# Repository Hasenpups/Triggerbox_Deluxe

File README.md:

Shield: [![CC BY-NC-SA 4.0][cc-by-nc-sa-shield]][cc-by-nc-sa]

This work is licensed under a
[Creative Commons Attribution-NonCommercial-ShareAlike 4.0 International License][cc-by-nc-sa].

[![CC BY-NC-SA 4.0][cc-by-nc-sa-image]][cc-by-nc-sa]

[cc-by-nc-sa]: http://creativecommons.org/licenses/by-nc-sa/4.0/
[cc-by-nc-sa-image]: https://licensebuttons.net/l/by-nc-sa/4.0/88x31.png
[cc-by-nc-sa-shield]: https://img.shields.io/badge/License-CC%20BY--NC--SA%204.0-lightgrey.svg

## Donations / Spenden
If somebody wants to support me for upcoming projects :)  
- PayPal:  
- Amazon Giftcard: https://www.amazon.de/Amazon-Gutschein-per-E-Mail-Amazon/dp/B0054PDOV8 - stefan.riese@me.com

# Triggerbox Deluxe

It's a trigger device for multiple devices and input counter.
- Raspberry Pi Pico
- 24V power input
- 8 x optocoupler input
- 8 x high side switch 24V 500mA output
- optional Wifi interface instead of USB connection (ESP32C3)

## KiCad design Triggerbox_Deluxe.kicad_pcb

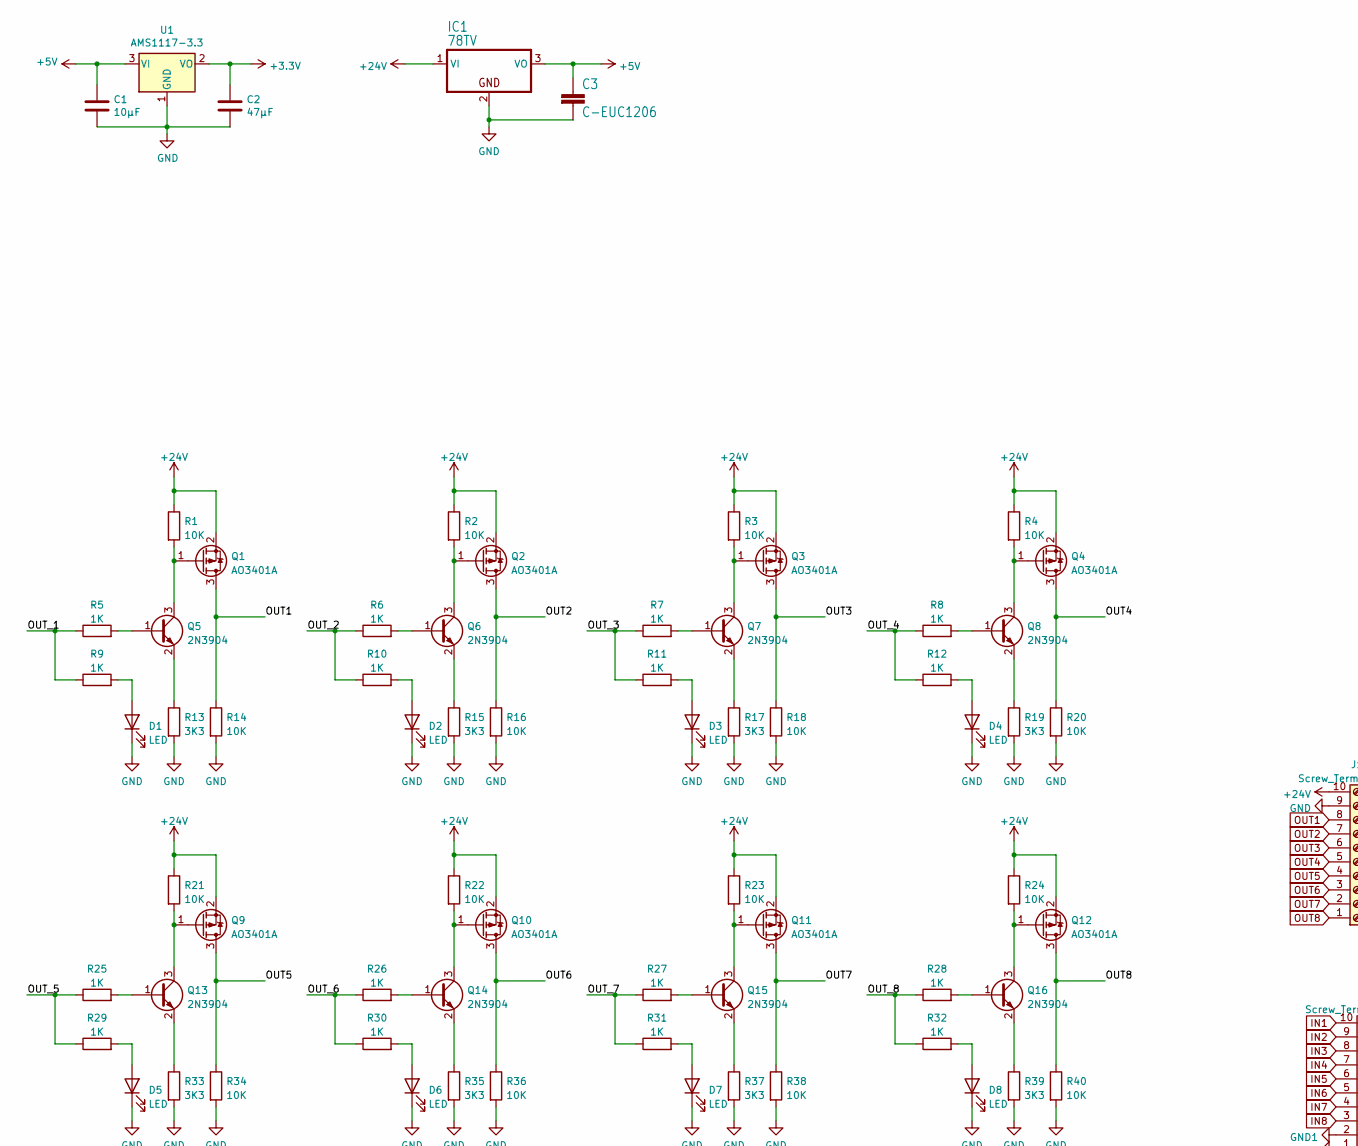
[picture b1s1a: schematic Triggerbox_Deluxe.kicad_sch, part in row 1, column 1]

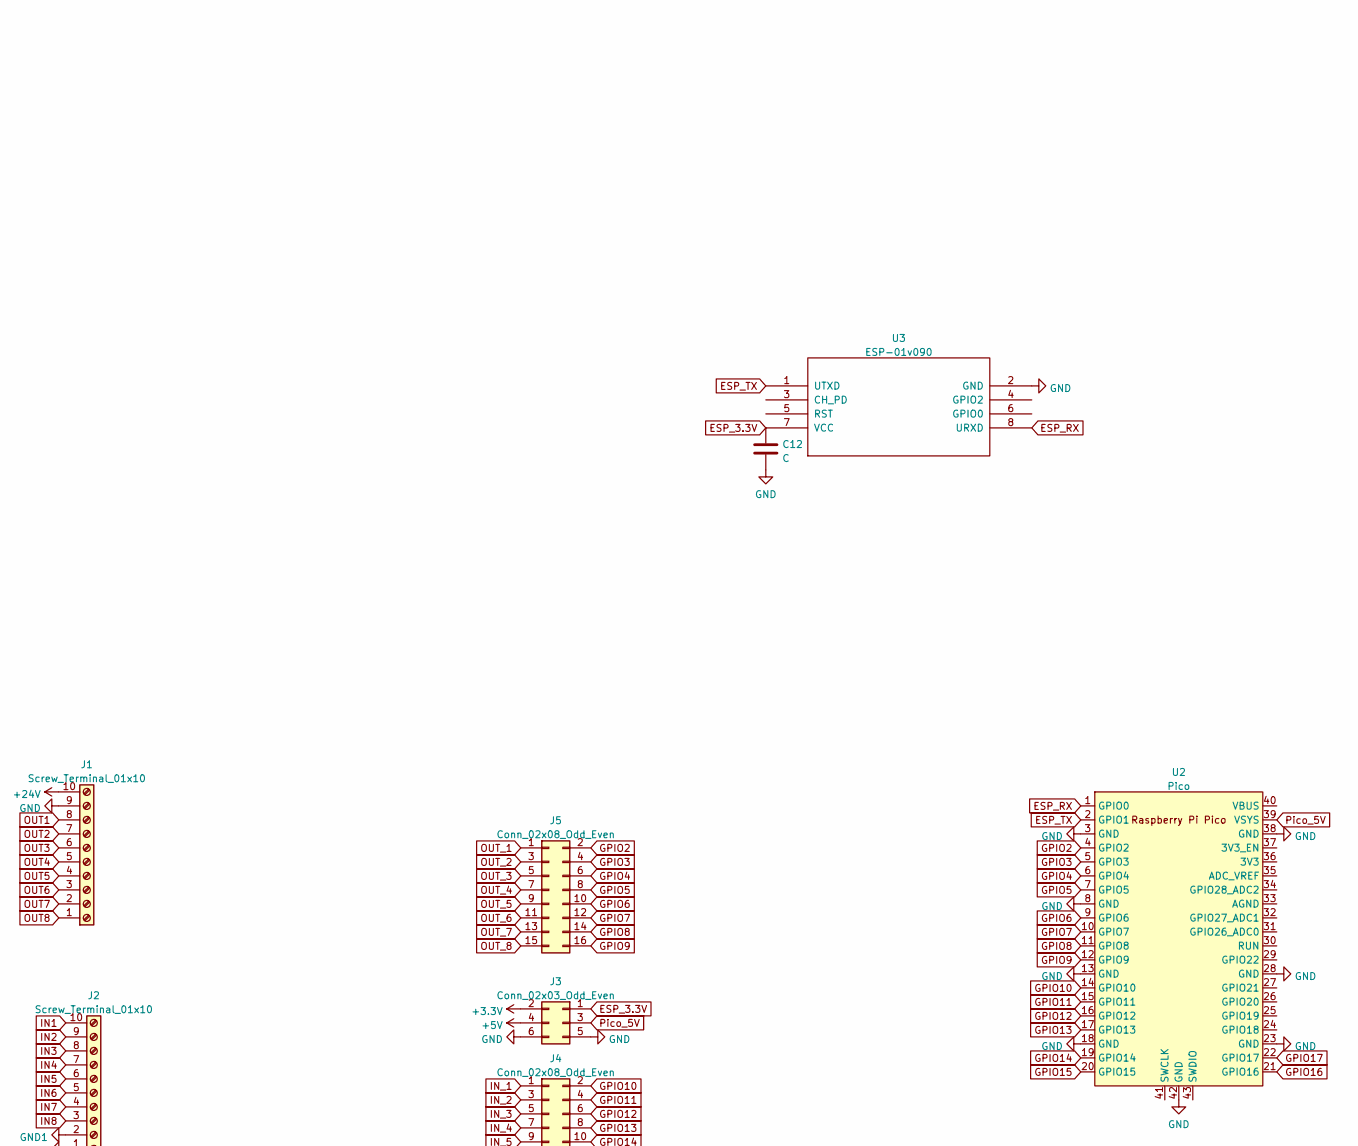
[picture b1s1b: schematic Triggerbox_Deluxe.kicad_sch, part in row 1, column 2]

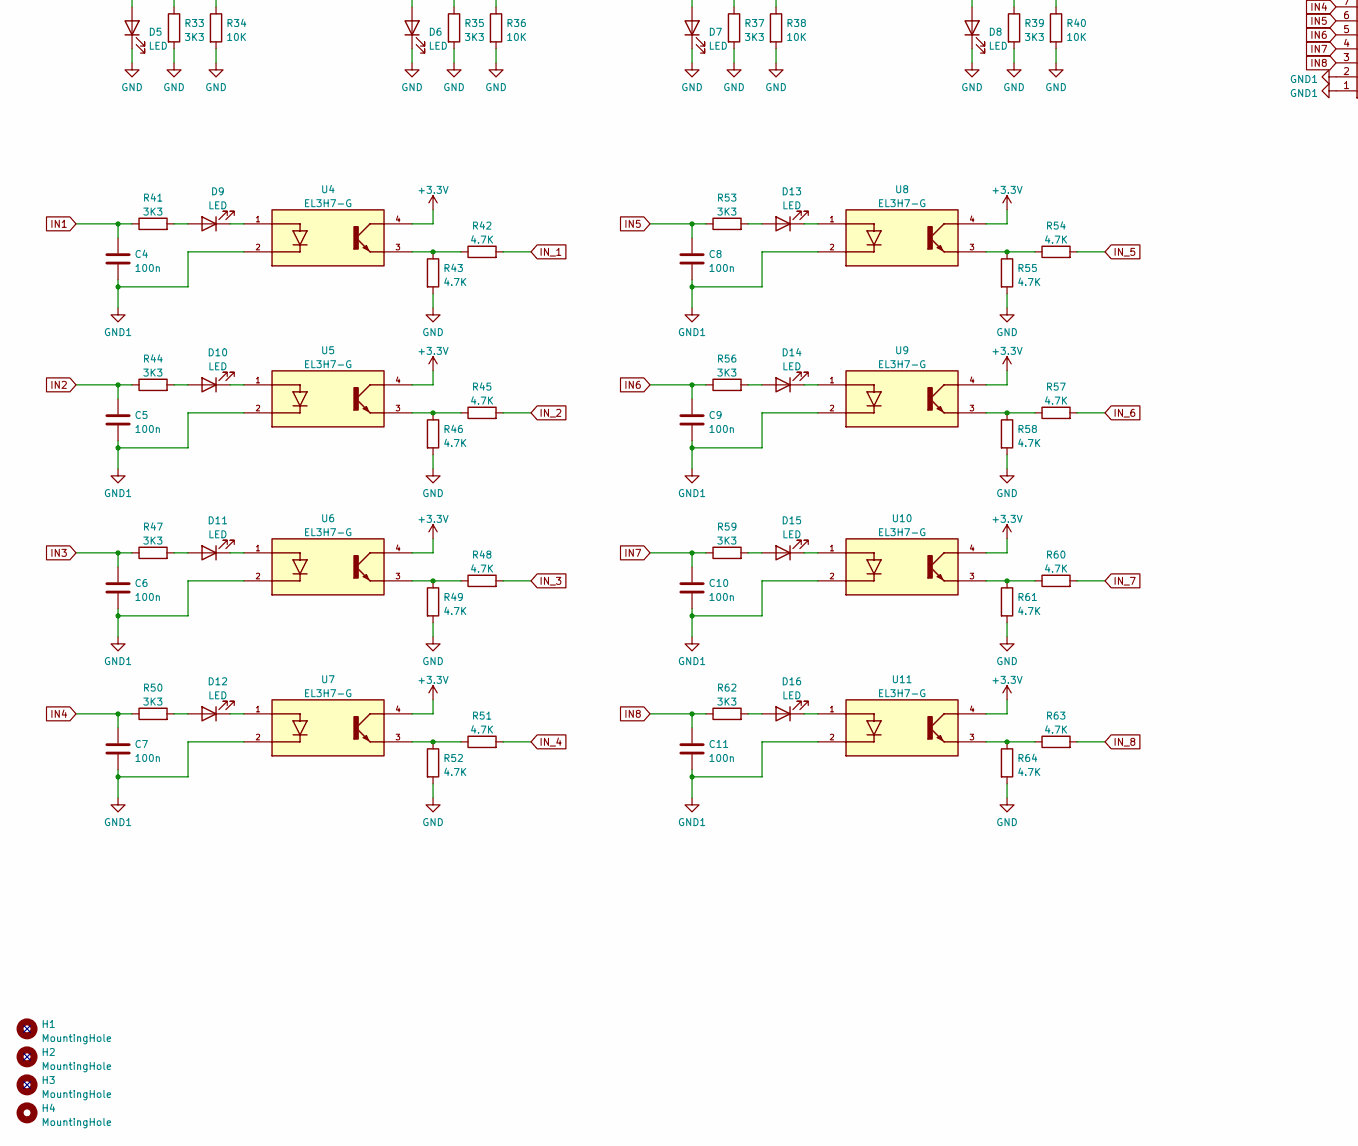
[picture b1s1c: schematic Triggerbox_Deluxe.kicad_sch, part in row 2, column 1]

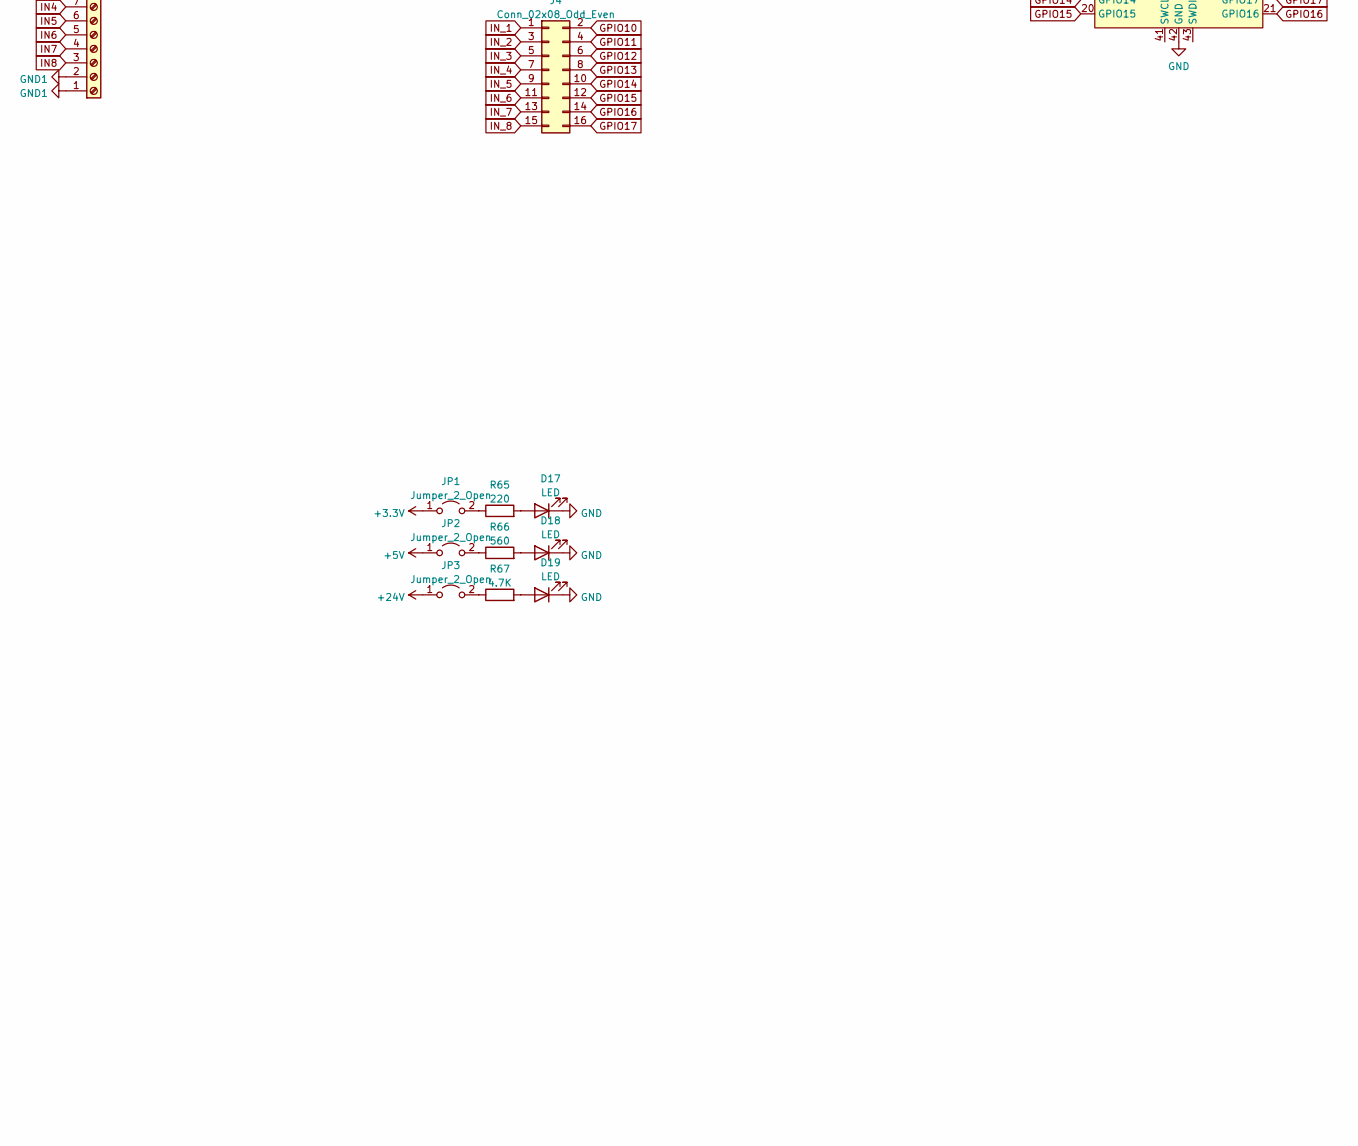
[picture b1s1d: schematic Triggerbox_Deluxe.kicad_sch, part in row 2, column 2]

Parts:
C1: 10µF; C_0603_1608Metric; LCSC C19702
C2: 47µF; C_0805_2012Metric; LCSC C16780
C3: C-EUC1206; C_1206_3216Metric
C4, C5, C6, C7, C8, C9, C10, C11: 100n; C_0805_2012Metric_Pad1.18x1.45mm_HandSolder; LCSC C49678
C12: C; C_1206_3216Metric_Pad1.33x1.80mm_HandSolder
D1, D2, D3, D4, D5, D6, D7, D8, D9, D10, D11, D12, D13, D14, D15, D16, D17, D18, D19: LED; LED_0805_2012Metric; LCSC C84256
H1, H2, H3, H4: MountingHole; MountingHole_3.2mm_M3_DIN965_Pad
IC1: 78TV; TO-220-3_Horizontal_TabUp
J1, J2: Screw_Terminal_01x10; TerminalBlock_Phoenix_MKDS-1,5-10-5.08_1x10_P5.08mm_Horizon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
J3: Conn_02x03_Odd_Even; PinHeader_2x03_P2.54mm_Vertical
J4, J5: Conn_02x08_Odd_Even; PinHeader_2x08_P2.54mm_Vertical
JP1, JP2, JP3: Jumper_2_Open; PinHeader_1x02_P2.54mm_Vertical
Q1, Q2, Q3, Q4, Q9, Q10, Q11, Q12: AO3401A; SOT-23; LCSC C15127
Q5, Q6, Q7, Q8, Q13, Q14, Q15, Q16: 2N3904; SOT-23; LCSC C20526
R1, R2, R3, R4, R14, R16, R18, R20, R21, R22, R23, R24, R34, R36, R38, R40: 10K; R_0603_1608Metric; LCSC C25804
R5, R6, R7, R8, R9, R10, R11, R12, R25, R26, R27, R28, R29, R30, R31, R32: 1K; R_0603_1608Metric; LCSC C21190
R13, R15, R17, R19, R33, R35, R37, R39, R41, R44, R47, R50, R53, R56, R59, R62: 3K3; R_0603_1608Metric; LCSC C22978
R42, R43, R45, R46, R48, R49, R51, R52, R54, R55, R57, R58, R60, R61, R63, R64, R67: 4.7K; R_0603_1608Metric; LCSC C23162
R65: 220; R_0603_1608Metric; LCSC C22962
R66: 560; R_0603_1608Metric; LCSC C23204
U1: AMS1117-3.3; SOT-223-3_TabPin2; LCSC C6186
U2: Pico; RPi_Pico_SMD_TH
U3: ESP-01v090; ESP-01
U4, U5, U6, U7, U8, U9, U10, U11: EL3H7-G; SOIC127P700X200-4N; PARTREV 7; LCSC C32565

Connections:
+3.3V: C2.1, J3.2, JP1.1 (A), U1.2 (VO), U4.4, U5.4, U6.4, U7.4, U8.4, U9.4, U10.4, U11.4
+5V: C1.1, C3.1, IC1.3 (VO), J3.4, JP2.1 (A), U1.3 (VI)
+24V: IC1.1 (VI), J1.10, JP3.1 (A), Q1.2 (S), Q2.2 (S), Q3.2 (S), Q4.2 (S), Q9.2 (S), Q10.2 (S), Q11.2 (S), Q12.2 (S), R1.1, R2.1, R3.1, R4.1, R21.1, R22.1, R23.1, R24.1
ESP_3.3V: C12.1, J3.1, U3.7 (VCC)
ESP_RX: U2.1 (GPIO0), U3.8 (URXD)
ESP_TX: U2.2 (GPIO1), U3.1 (UTXD)
GND: C1.2, C2.2, C3.2, C12.2, D1.1 (K), D2.1 (K), D3.1 (K), D4.1 (K), D5.1 (K), D6.1 (K), D7.1 (K), D8.1 (K), D17.1 (K), D18.1 (K), D19.1 (K), IC1.2 (GND), J1.9, J3.5, J3.6, R13.2, R14.2, R15.2, R16.2, R17.2, R18.2, R19.2, R20.2, R33.2, R34.2, R35.2, R36.2, R37.2, R38.2, R39.2, R40.2, R43.2, R46.2, R49.2, R52.2, R55.2, R58.2, R61.2, R64.2, U1.1 (GND), U2.3 (GND), U2.8 (GND), U2.13 (GND), U2.18 (GND), U2.23 (GND), U2.28 (GND), U2.38 (GND), U2.42 (GND), U3.2 (GND)
GND1: C4.2, C5.2, C6.2, C7.2, C8.2, C9.2, C10.2, C11.2, J2.1, J2.2, U4.2, U5.2, U6.2, U7.2, U8.2, U9.2, U10.2, U11.2
GPIO2: J5.2, U2.4 (GPIO2)
GPIO3: J5.4, U2.5 (GPIO3)
GPIO4: J5.6, U2.6 (GPIO4)
GPIO5: J5.8, U2.7 (GPIO5)
GPIO6: J5.10, U2.9 (GPIO6)
GPIO7: J5.12, U2.10 (GPIO7)
GPIO8: J5.14, U2.11 (GPIO8)
GPIO9: J5.16, U2.12 (GPIO9)
GPIO10: J4.2, U2.14 (GPIO10)
GPIO11: J4.4, U2.15 (GPIO11)
GPIO12: J4.6, U2.16 (GPIO12)
GPIO13: J4.8, U2.17 (GPIO13)
GPIO14: J4.10, U2.19 (GPIO14)
GPIO15: J4.12, U2.20 (GPIO15)
GPIO16: J4.14, U2.21 (GPIO16)
GPIO17: J4.16, U2.22 (GPIO17)
IN1: C4.1, J2.10, R41.1
IN2: C5.1, J2.9, R44.1
IN3: C6.1, J2.8, R47.1
IN4: C7.1, J2.7, R50.1
IN5: C8.1, J2.6, R53.1
IN6: C9.1, J2.5, R56.1
IN7: C10.1, J2.4, R59.1
IN8: C11.1, J2.3, R62.1
IN_1: J4.1, R42.2
IN_2: J4.3, R45.2
IN_3: J4.5, R48.2
IN_4: J4.7, R51.2
IN_5: J4.9, R54.2
IN_6: J4.11, R57.2
IN_7: J4.13, R60.2
IN_8: J4.15, R63.2
unnamed: D1.2 (A), R9.2
unnamed: D2.2 (A), R10.2
unnamed: D3.2 (A), R11.2
unnamed: D4.2 (A), R12.2
unnamed: D5.2 (A), R29.2
unnamed: D6.2 (A), R30.2
unnamed: D7.2 (A), R31.2
unnamed: D8.2 (A), R32.2
unnamed: D9.1 (K), U4.1
unnamed: D9.2 (A), R41.2
unnamed: D10.1 (K), U5.1
unnamed: D10.2 (A), R44.2
unnamed: D11.1 (K), U6.1
unnamed: D11.2 (A), R47.2
unnamed: D12.1 (K), U7.1
unnamed: D12.2 (A), R50.2
unnamed: D13.1 (K), U8.1
unnamed: D13.2 (A), R53.2
unnamed: D14.1 (K), U9.1
unnamed: D14.2 (A), R56.2
unnamed: D15.1 (K), U10.1
unnamed: D15.2 (A), R59.2
unnamed: D16.1 (K), U11.1
unnamed: D16.2 (A), R62.2
unnamed: D17.2 (A), R65.2
unnamed: D18.2 (A), R66.2
unnamed: D19.2 (A), R67.2
unnamed: JP1.2 (B), R65.1
unnamed: JP2.2 (B), R66.1
unnamed: JP3.2 (B), R67.1
unnamed: Q1.1 (G), Q5.3 (C), R1.2
unnamed: Q2.1 (G), Q6.3 (C), R2.2
unnamed: Q3.1 (G), Q7.3 (C), R3.2
unnamed: Q4.1 (G), Q8.3 (C), R4.2
unnamed: Q5.1 (B), R5.2
unnamed: Q5.2 (E), R13.1
unnamed: Q6.1 (B), R6.2
unnamed: Q6.2 (E), R15.1
unnamed: Q7.1 (B), R7.2
unnamed: Q7.2 (E), R17.1
unnamed: Q8.1 (B), R8.2
unnamed: Q8.2 (E), R19.1
unnamed: Q10.1 (G), Q14.3 (C), R22.2
unnamed: Q11.1 (G), Q15.3 (C), R23.2
unnamed: Q12.1 (G), Q16.3 (C), R24.2
unnamed: Q13.1 (B), R25.2
unnamed: Q13.2 (E), R33.1
unnamed: Q9.1 (G), Q13.3 (C), R21.2
unnamed: Q14.1 (B), R26.2
unnamed: Q14.2 (E), R35.1
unnamed: Q15.1 (B), R27.2
unnamed: Q15.2 (E), R37.1
unnamed: Q16.1 (B), R28.2
unnamed: Q16.2 (E), R39.1
unnamed: R42.1, R43.1, U4.3
unnamed: R45.1, R46.1, U5.3
unnamed: R48.1, R49.1, U6.3
unnamed: R51.1, R52.1, U7.3
unnamed: R54.1, R55.1, U8.3
unnamed: R57.1, R58.1, U9.3
unnamed: R60.1, R61.1, U10.3
unnamed: R63.1, R64.1, U11.3
OUT1: J1.8, Q1.3 (D), R14.1
OUT2: J1.7, Q2.3 (D), R16.1
OUT3: J1.6, Q3.3 (D), R18.1
OUT4: J1.5, Q4.3 (D), R20.1
OUT5: J1.4, Q9.3 (D), R34.1
OUT6: J1.3, Q10.3 (D), R36.1
OUT7: J1.2, Q11.3 (D), R38.1
OUT8: J1.1, Q12.3 (D), R40.1
OUT_1: J5.1, R5.1, R9.1
OUT_2: J5.3, R6.1, R10.1
OUT_3: J5.5, R7.1, R11.1
OUT_4: J5.7, R8.1, R12.1
OUT_5: J5.9, R25.1, R29.1
OUT_6: J5.11, R26.1, R30.1
OUT_7: J5.13, R27.1, R31.1
OUT_8: J5.15, R28.1, R32.1
Pico_5V: J3.3, U2.39 (VSYS)

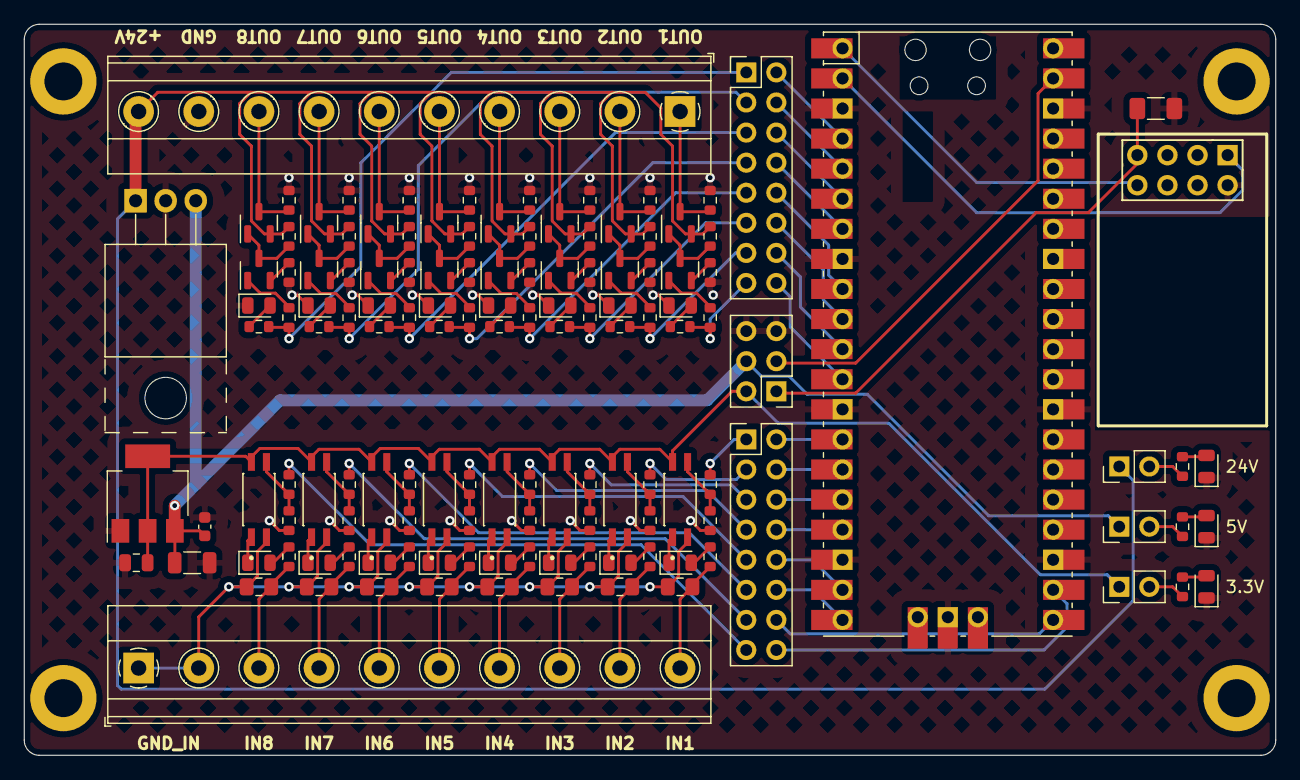
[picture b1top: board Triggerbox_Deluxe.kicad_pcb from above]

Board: 2 copper layers, 105.7 x 61.7 mm, 138 parts (0 on the bottom side), 119 nets.

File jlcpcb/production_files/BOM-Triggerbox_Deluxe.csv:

Comment,Designator,Footprint,LCSC
AO3401A,"Q1,Q10,Q11,Q12,Q2,Q3,Q4,Q9",SOT-23,C15127
47µF,C2,C_0805_2012Metric,C16780
10µF,C1,C_0603_1608Metric,C19702
2N3904,"Q13,Q14,Q15,Q16,Q5,Q6,Q7,Q8",SOT-23,C20526
1K,"R10,R11,R12,R25,R26,R27,R28,R29,R30,R31,R32,R5,R6,R7,R8,R9",R_0603_1608Metric,C21190
220,R65,R_0603_1608Metric,C22962
3K3,"R13,R15,R17,R19,R33,R35,R37,R39,R41,R44,R47,R50,R53,R56,R59,R62",R_0603_1608Metric,C22978
4.7K,"R42,R43,R45,R46,R48,R49,R51,R52,R54,R55,R57,R58,R60,R61,R63,R64,R67",R_0603_1608Metric,C23162
560,R66,R_0603_1608Metric,C23204
10K,"R1,R14,R16,R18,R2,R20,R21,R22,R23,R24,R3,R34,R36,R38,R4,R40",R_0603_1608Metric,C25804
EL3H7-G,"U10,U11,U4,U5,U6,U7,U8,U9",SOIC127P700X200-4N,C32565
100n,"C10,C11,C4,C5,C6,C7,C8,C9",C_0805_2012Metric_Pad1.18x1.45mm_HandSolder,C49678
AMS1117-3.3,U1,SOT-223-3_TabPin2,C6186
LED,"D1,D10,D11,D12,D13,D14,D15,D16,D17,D18,D19,D2,D3,D4,D5,D6,D7,D8,D9",LED_0805_2012Metric,C84256
Conn_02x08_Odd_Even,J4,PinHeader_2x08_P2.54mm_Vertical,
Conn_02x03_Odd_Even,J3,PinHeader_2x03_P2.54mm_Vertical,
MountingHole,H1,MountingHole_3.2mm_M3_DIN965_Pad,
78TV,IC1,TO-220-3_Horizontal_TabUp,
MountingHole,H4,MountingHole_3.2mm_M3_DIN965_Pad,
MountingHole,H3,MountingHole_3.2mm_M3_DIN965_Pad,
C-EUC1206,C3,C_1206_3216Metric,
Screw_Terminal_01x10,J1,"TerminalBlock_Phoenix_MKDS-1,5-10-5.08_1x10_P5.08mm_Horizontal",
Screw_Terminal_01x10,J2,"TerminalBlock_Phoenix_MKDS-1,5-10-5.08_1x10_P5.08mm_Horizontal",
MountingHole,H2,MountingHole_3.2mm_M3_DIN965_Pad,
C,C12,C_1206_3216Metric_Pad1.33x1.80mm_HandSolder,
ESP-01v090,U3,ESP-01,
Conn_02x08_Odd_Even,J5,PinHeader_2x08_P2.54mm_Vertical,
Pico,U2,RPi_Pico_SMD_TH,
Jumper_2_Open,JP3,PinHeader_1x02_P2.54mm_Vertical,
Jumper_2_Open,JP2,PinHeader_1x02_P2.54mm_Vertical,
Jumper_2_Open,JP1,PinHeader_1x02_P2.54mm_Vertical,

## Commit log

2023-03-20 - initial commit
2023-03-20 - commit license
